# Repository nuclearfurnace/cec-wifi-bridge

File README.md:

# cec-wifi-bridge
A WiFi-enabled HDMI dongle for issuing CEC commands.

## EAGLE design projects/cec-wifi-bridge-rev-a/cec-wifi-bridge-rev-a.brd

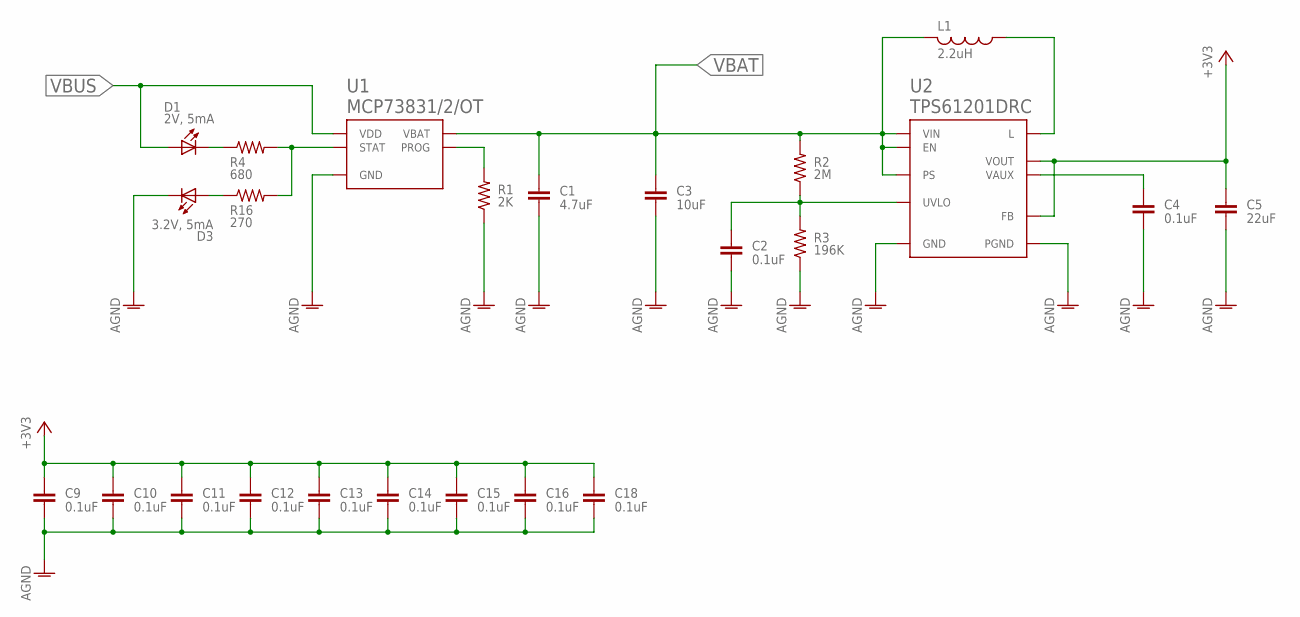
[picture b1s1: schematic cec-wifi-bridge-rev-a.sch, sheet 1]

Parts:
C1: 4.7uF; C0603
C2, C4, C9, C10, C11, C12, C13, C14, C15, C16, C18: 0.1uF; C0402
C3: 10uF; C0805
C5: 22uF; C0805
D1: 2V, 5mA; DIALIGHT-0603
D3: 3.2V, 5mA; DIALIGHT-0603
L1: 2.2uH; COILCRAFT-XPL2010
R1: 2K; R0402
R2: 2M; R0402
R3: 196K; R0402
R4: 680; R0603
R16: 270; R0603
U1: MCP73831/2/OT; 5-SOT23
U2: TPS61201DRC; S-PVSON-N10-DRC

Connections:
+3V3: C5.1, C9.1, C10.1, C11.1, C12.1, C13.1, C14.1, C15.1, C16.1, C18.1, U2.P$2 (VOUT), U2.P$10 (FB); also elsewhere on the board
AGND: C1.2, C2.2, C3.2, C4.2, C5.2, C9.2, C10.2, C11.2, C12.2, C13.2, C14.2, C15.2, C16.2, C18.2, D3.2 (C), R1.1, R3.1, U1.2 (GND), U2.GND-VIA-1 (PGND), U2.GND-VIA-2 (PGND), U2.GND-VIA-3 (PGND), U2.GND-VIA-4 (PGND), U2.GND-VIA-5 (PGND), U2.P$4 (PGND), U2.P$9 (GND), U2.THERMAL (PGND), U2.THERMAL1 (PGND), U2.THERMAL2 (PGND), U2.THERMAL3 (PGND), U2.THERMAL4 (PGND); also elsewhere on the board
unnamed: C4.1, U2.P$1 (VAUX)
unnamed: R1.2, U1.5 (PROG)
unnamed: D3.1 (A), R16.1
unnamed: C2.1, R2.1, R3.2, U2.P$7 (UVLO)
unnamed: R4.2, R16.2, U1.1 (STAT)
unnamed: D1.2 (C), R4.1
unnamed: L1.P$1 (1), U2.P$3 (L)
VBAT: C1.1, C3.1, L1.P$2 (2), R2.2, U1.3 (VBAT), U2.P$5 (VIN), U2.P$6 (EN), U2.P$8 (PS); also elsewhere on the board
VBUS: D1.1 (A), U1.4 (VDD); also elsewhere on the board

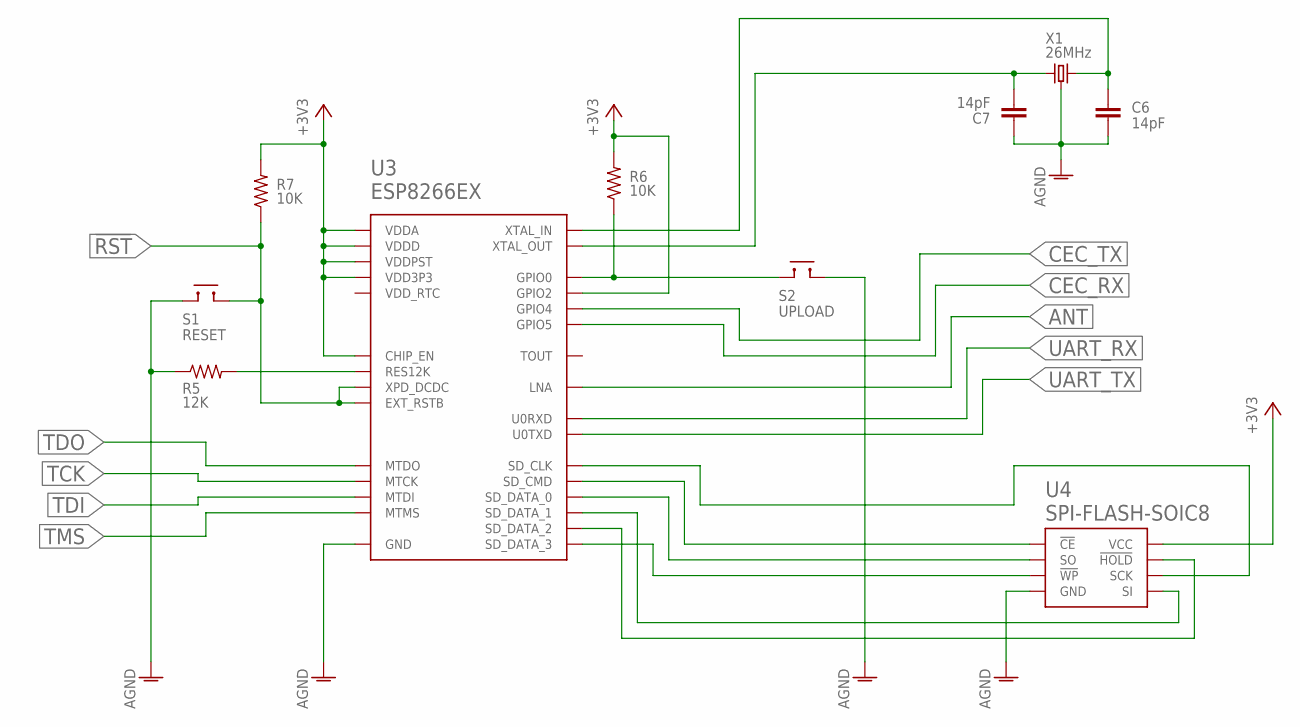
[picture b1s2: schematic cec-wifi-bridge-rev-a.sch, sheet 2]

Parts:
C6, C7: 14pF; C0402
R5: 12K; R0402
R6, R7: 10K; R0402
S1: RESET; ALPS-SKQG
S2: UPLOAD; ALPS-SKQG
U3: ESP8266EX
U4: SPI-FLASH-SOIC8; SOIC-8
X1: 26MHz; EPSON-TSX-3225

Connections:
!RST: R7.1, S1.P$3, S1.P$4, U3.EXT_RSTB, U3.XPD_DCDC; also elsewhere on the board
+3V3: R6.2, R7.2, U3.CHIP_EN, U3.GPIO2, U3.VDD3P3, U3.VDD3P3$2 (VDD3P3), U3.VDDA, U3.VDDA$2 (VDDA), U3.VDDD, U3.VDDPST, U3.VDDPST$2 (VDDPST), U4.P$8 (VCC); also elsewhere on the board
AGND: C6.2, C7.1, R5.1, S1.P$1, S1.P$2, S2.P$3, S2.P$4, U3.GND, U3.P$1 (GND), U3.P$2 (GND), U3.P$3 (GND), U3.P$4 (GND), U3.P$5 (GND), U3.P$6 (GND), U3.P$7 (GND), U3.P$8 (GND), U3.P$9 (GND), U4.P$4 (GND), X1.P$2 (GND), X1.P$4 (GND); also elsewhere on the board
ANT: U3.LNA; also elsewhere on the board
CEC_RX: U3.GPOIO5 (GPIO5); also elsewhere on the board
CEC_TX: U3.GPIO4; also elsewhere on the board
FLASH_BOOT: R6.1, S2.P$1, S2.P$2, U3.GPIO0
unnamed: R5.2, U3.RES12K
unnamed: C6.1, U3.XTAL_IN, X1.P$3 (2)
unnamed: C7.2, U3.XTAL_OUT, X1.P$1 (1)
unnamed: U3.SD_CLK, U4.P$6 (SCK)
unnamed: U3.SD_CMD, U4.P$1 (!CE)
unnamed: U3.SD_DATA_1, U4.P$5 (SI)
unnamed: U3.SD_DATA_0, U4.P$2 (SO)
unnamed: U3.SD_DATA_3, U4.P$3 (!WP)
unnamed: U3.SD_DATA_2, U4.P$7 (!HOLD)
TCK: U3.MTCK; also elsewhere on the board
TDI: U3.MTDI; also elsewhere on the board
TDO: U3.MTDO; also elsewhere on the board
TMS: U3.MTMS; also elsewhere on the board
UART_RX: U3.U0RXD; also elsewhere on the board
UART_TX: U3.U0TXD; also elsewhere on the board

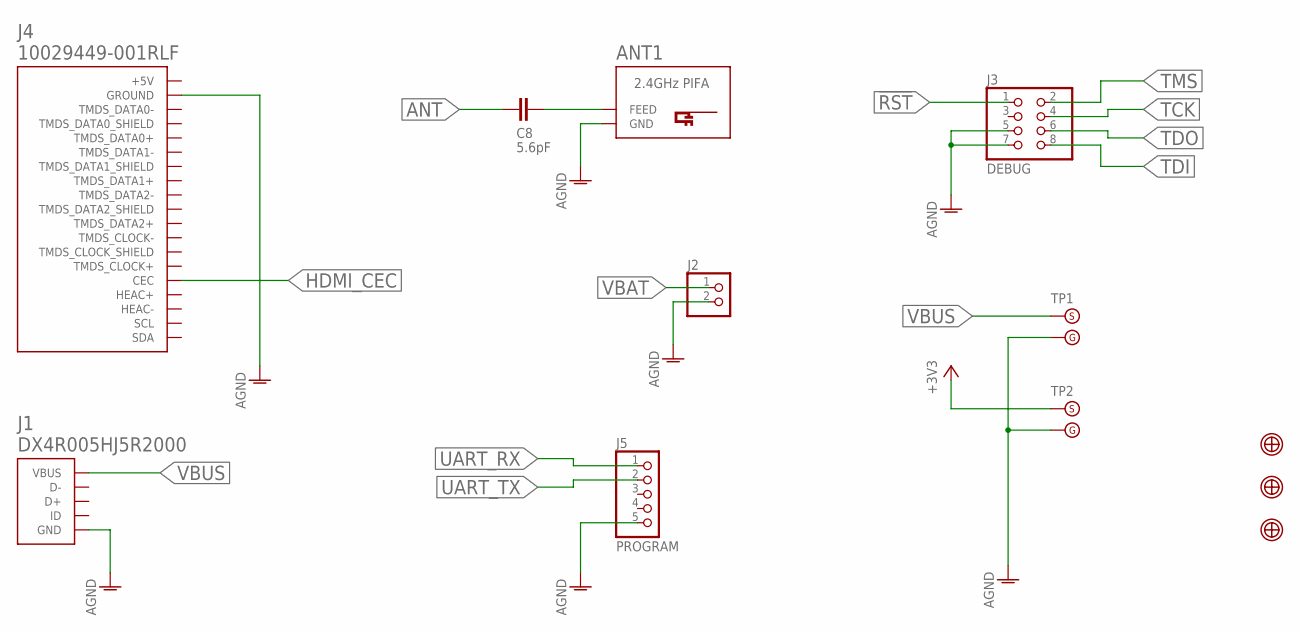
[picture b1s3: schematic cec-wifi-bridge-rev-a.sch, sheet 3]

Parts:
ANT1: INVERTED_F_ANTENNA+0; DN007+0
C8: 5.6pF; C0402
J1: DX4R005HJ5R2000
J2: PINHD-1X2; 1X02
J3: DEBUG; 2X04
J4: 10029449-001RLF; 10029449
J5: PROGRAM; 1X05
TP1, TP2: TESTPOINT-WITH-GND; TESTPOINT-1.5-WITH-GND
U$1, U$2, U$3: FIDUCIAL-1MM; FIDUCIAL_1MM

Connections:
!RST: J3.1; also elsewhere on the board
+3V3: TP2.S; also elsewhere on the board
AGND: ANT1.GND, ANT1.GND@1 (GND), J1.5 (GND), J1.CASE_1 (GND), J1.CASE_2 (GND), J1.CASE_3 (GND), J1.CASE_4 (GND), J2.2, J3.5, J3.7, J4.P$17 (GROUND), J5.5, TP1.G, TP2.G; also elsewhere on the board
ANT: C8.1; also elsewhere on the board
HDMI_CEC: J4.P$13 (CEC); also elsewhere on the board
unnamed: ANT1.FEED, C8.2
TCK: J3.4; also elsewhere on the board
TDI: J3.8; also elsewhere on the board
TDO: J3.6; also elsewhere on the board
TMS: J3.2; also elsewhere on the board
UART_RX: J5.1; also elsewhere on the board
UART_TX: J5.2; also elsewhere on the board
VBAT: J2.1; also elsewhere on the board
VBUS: J1.1 (VBUS), TP1.S; also elsewhere on the board

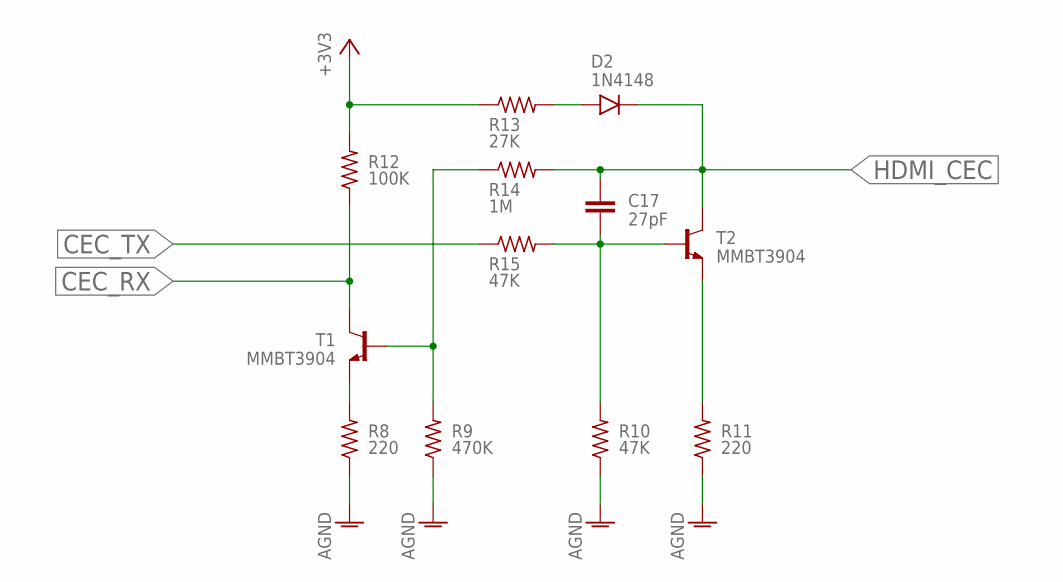
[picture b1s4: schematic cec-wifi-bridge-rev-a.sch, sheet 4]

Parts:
C17: 27pF; C0402
D2: 1N4148; SOD123
R8, R11: 220; R0402
R9: 470K; R0402
R10, R15: 47K; R0402
R12: 100K; R0402
R13: 27K; R0402
R14: 1M; R0402
T1, T2: MMBT3904; SOT-23

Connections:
+3V3: R12.2, R13.1; also elsewhere on the board
AGND: R8.1, R9.1, R10.1, R11.1; also elsewhere on the board
CEC_RX: R12.1, T1.P$3 (C); also elsewhere on the board
CEC_TX: R15.1; also elsewhere on the board
HDMI_CEC: C17.1, D2.C, R14.2, T2.P$3 (C); also elsewhere on the board
unnamed: C17.2, R10.2, R15.2, T2.P$1 (B)
unnamed: R8.2, T1.P$2 (E)
unnamed: R9.2, R14.1, T1.P$1 (B)
unnamed: D2.A, R13.2
unnamed: R11.2, T2.P$2 (E)

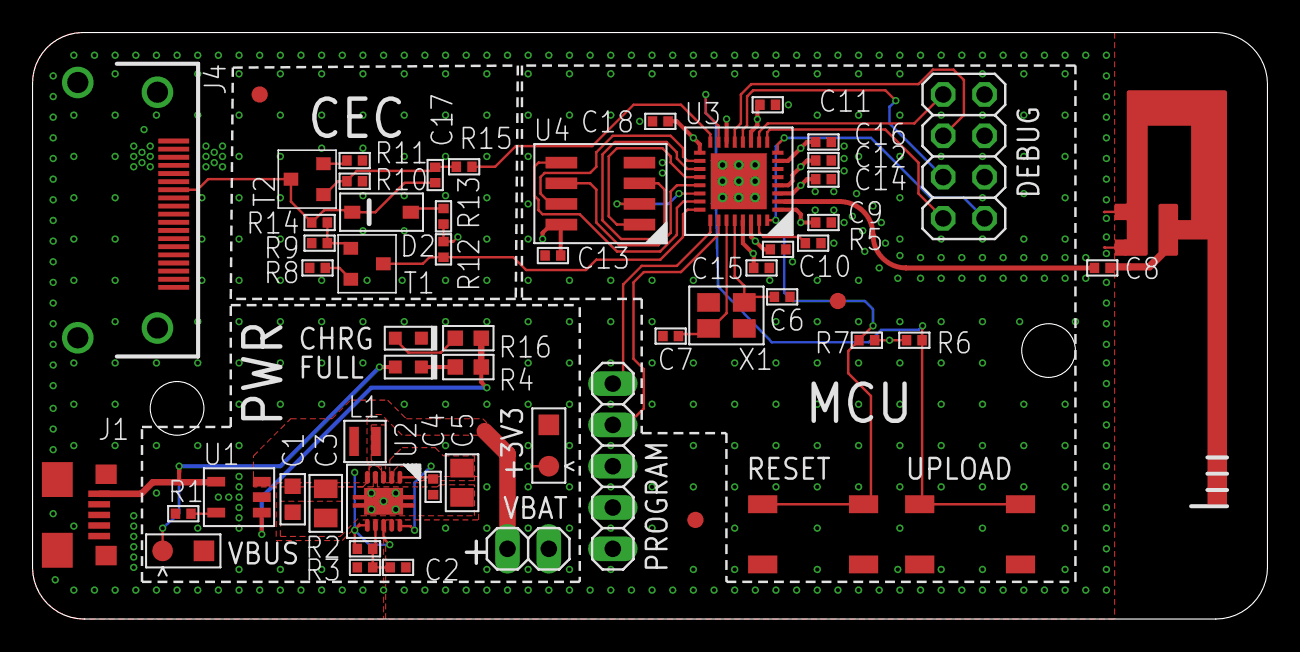
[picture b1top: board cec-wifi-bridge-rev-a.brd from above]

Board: 4 copper layers, 75.9 x 36.1 mm, 58 parts (0 on the bottom side), 38 nets.

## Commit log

2017-01-21 Initial commit of the rev A design.
    Right now we just have the power supply and battery charging section
    done.
2017-01-21 Repository streamlining.
    Making this match our other Eagle projects, including directory
    structure and automated tests.
2017-01-21 Bad path to schematic.
2017-01-22 Starting to add in the main bits.
2017-01-23 Start wiring up the ESP8266.
2017-01-26 Lots of tweaks and changes.
2017-01-27 Lots of board layout work.
    The board is basically done.
    It has a real shape now, things are laid out. We have fiducials,
    alignment holes, rounded edges, the PCB antenna with the proper
    setbacks, ground plane stitching, we have our logo in place (!), and
    things are generally buttoned up.
    We still need to fill out the BOM entirely, as well as clean up the
2017-01-29 cleanup
2017-01-29 Filled in BOM and super stitched.
    Filled in all of the BOM values. Also stitches the hell out of the
    board. Realllly stitched it. Probably overstitched it.
2017-01-31 Add BOM parts and adjust alignment holes.
    Added the remaining two BOM values.
    Adjusted the location of the alignment pin holes so that we can cleanly
    fit the LiPo battery on the underside of the board without it being
    under the PCB antenna and without it being too close to the HDMI
    through-hole pins.
2017-02-01 Add LED and more board tweaking.
    Added another LED after realizing that STAT on the battery charger IC is
    actually tri-state -- thanks, Adafruit! This means we can now show when
    the battery is charging and when it's full, wee!
    Also moved bits and pieces around on the board. Spread out the
    stitching vias, moved vias out of the way of the silkscreen, etc etc.
2017-02-04 Generating MCAD files and prepping to start the enclosure design.
2017-02-04 Switch to DX4R005HJ5R2000 for USB connector.
    The other version we were using had no 3D model available from JAE, so I
    found one that did, so we can properly design the enclosure and model it
    all assembled.
2017-02-04 Start adding in the MCAD files.
    I did a rough import that got the board into an MCAD state. We have
    both connectors modeled properly, so now we can start to work on a
    design for the enclosure.
2017-02-06 Created an enclosure for the circuit board.
    I whipped up a simple enclosure for the board in SolidWorks. Some of
    the features:
    - has enough space under the board for the LiPo battery to be nestled
    - locating pins to lock the board in place
    - snap hooks for toolless assembly
    I'm pretty sure we should be able to 3D print this, although the feature
2017-02-06 Generate 3D STL versions of the top and bottom pieces.
    Just turned off some planes from view and then generated STL versions of
    the top and bottom pieces so we can get this printed.
2017-02-06 Add part number for ESP8266.
2017-02-07 More sane stitching.
    The stitching before was haphazard, ugly, overkill, and generally
    wasteful. I did a more sane and uniform stitching of ground.
    Looks better, and I'm guessing things will function just the same.
2017-02-09 Fixing up the alignment of the USB port with the actuality of the enclosure.
2017-02-09 Add testpoints for the power rails.
2017-02-09 Small stitching tweaks. Last tweaks, I promise!
2017-02-13 Final layout tweaks before locking rev A.
    We've given the TPS61200 its own power ground, hopefully quashing as
    much noise as possible off the main ground, keeping RF performance high.
    I lied, and went back to adjust the stitching. We should have our
    stitching on a 100 mil grid consistently, with a few exceptions to deal
    with component placement.
    Also fixed a bug where we had a decoupling cap on a configuration pin
2017-02-20 BOM tweaks to account for supply chain issues.
2017-03-05 Tweaks t to the enclosure dimensions.
    After getting prototypes made, there were a few design errors that
    needed to be corrected:
    - didn't include any tolerance for the locating pins
    - board was too snug of a fit between snap hooks to easily seat
    - edge fillets were too small and ended up more like chamfers
    - didn't propagate the HDMI connector cut-out to the assembly parts
2017-03-27 A few fixes after testing the rev A1 boards.
    Just fixing up a fix issues I found while build/testing the rev A1
    boards, namely:
    - using wrong footprint for T1/T2
    - LEDs way too bright; adjusted series resistors
    - used wrong part number for boost converter (ooof!)
    - shoved HDMI connector closer to the edge
